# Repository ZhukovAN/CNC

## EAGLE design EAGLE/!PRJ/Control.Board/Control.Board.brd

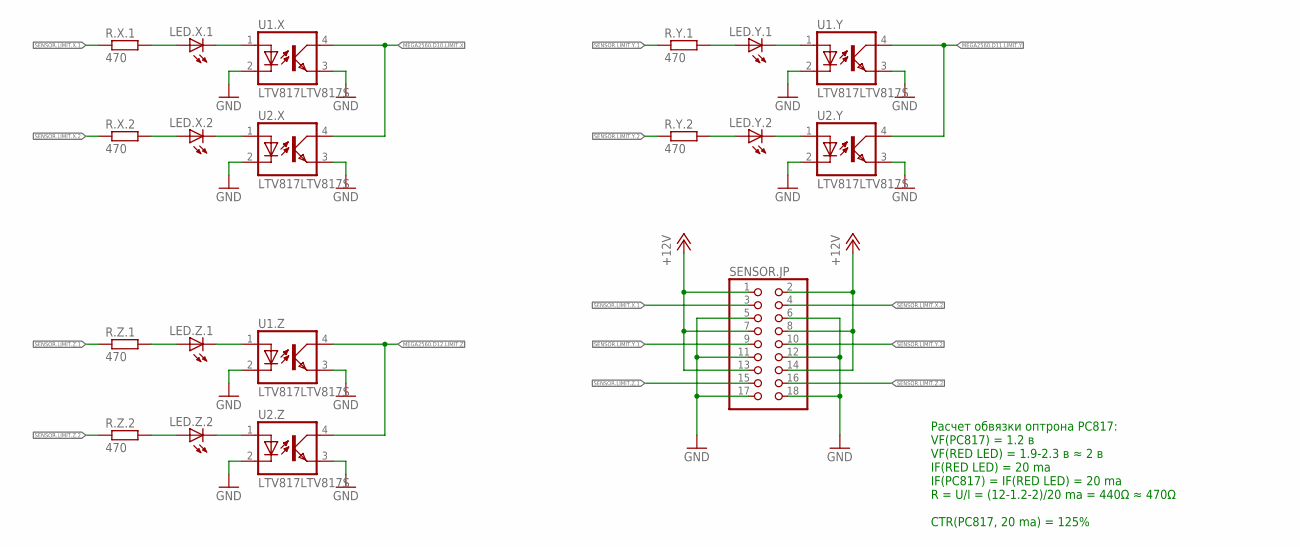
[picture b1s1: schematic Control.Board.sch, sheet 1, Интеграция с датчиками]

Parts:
LED.X.1, LED.X.2, LED.Y.1, LED.Y.2, LED.Z.1, LED.Z.2: LEDCHIPLED_1206; CHIPLED_1206
R.X.1, R.X.2, R.Y.1, R.Y.2, R.Z.1, R.Z.2: 470; M1206
SENSOR.JP: PINHD-2X9; 2X09
U1.X, U1.Y, U1.Z, U2.X, U2.Y, U2.Z: LTV817LTV817S; DIL4-SMD

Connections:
MEGA2560.D10.LIMIT.X: U1.X.4 (COL), U2.X.4 (COL); also elsewhere on the board
MEGA2560.D11.LIMIT.Y: U1.Y.4 (COL), U2.Y.4 (COL); also elsewhere on the board
MEGA2560.D12.LIMIT.Z: U1.Z.4 (COL), U2.Z.4 (COL); also elsewhere on the board
MEGA2560.GND: SENSOR.JP.5, SENSOR.JP.6, SENSOR.JP.11, SENSOR.JP.12, SENSOR.JP.17, SENSOR.JP.18, U1.X.2 (C), U1.X.3 (EMIT), U1.Y.2 (C), U1.Y.3 (EMIT), U1.Z.2 (C), U1.Z.3 (EMIT), U2.X.2 (C), U2.X.3 (EMIT), U2.Y.2 (C), U2.Y.3 (EMIT), U2.Z.2 (C), U2.Z.3 (EMIT); also elsewhere on the board
MEGA2560.VIN.12V: SENSOR.JP.1, SENSOR.JP.2, SENSOR.JP.7, SENSOR.JP.8, SENSOR.JP.13, SENSOR.JP.14; also elsewhere on the board
unnamed: LED.X.2.C, U2.X.1 (A)
unnamed: LED.Y.1.A, R.Y.1.2
unnamed: LED.X.1.A, R.X.1.2
unnamed: LED.X.2.A, R.X.2.2
unnamed: LED.X.1.C, U1.X.1 (A)
unnamed: LED.Y.2.A, R.Y.2.2
unnamed: LED.Y.2.C, U2.Y.1 (A)
unnamed: LED.Y.1.C, U1.Y.1 (A)
unnamed: LED.Z.1.A, R.Z.1.2
unnamed: LED.Z.2.A, R.Z.2.2
unnamed: LED.Z.2.C, U2.Z.1 (A)
unnamed: LED.Z.1.C, U1.Z.1 (A)
SENSOR.LIMIT.X.1: R.X.1.1, SENSOR.JP.3
SENSOR.LIMIT.X.2: R.X.2.1, SENSOR.JP.4
SENSOR.LIMIT.Y.1: R.Y.1.1, SENSOR.JP.9
SENSOR.LIMIT.Y.2: R.Y.2.1, SENSOR.JP.10
SENSOR.LIMIT.Z.1: R.Z.1.1, SENSOR.JP.15
SENSOR.LIMIT.Z.2: R.Z.2.1, SENSOR.JP.16

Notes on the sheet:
Расчет обвязки оптрона PC817: VF(PC817) = 1.2 в VF(RED LED) = 1.9-2.3 в ≈ 2 в IF(RED LED) = 20 ma IF(PC817) = IF(RED LED) = 20 ma R = U/I = (12-1.2-2)/20 ma = 440Ω ≈ 470Ω CTR(PC817, 20 ma) = 125%

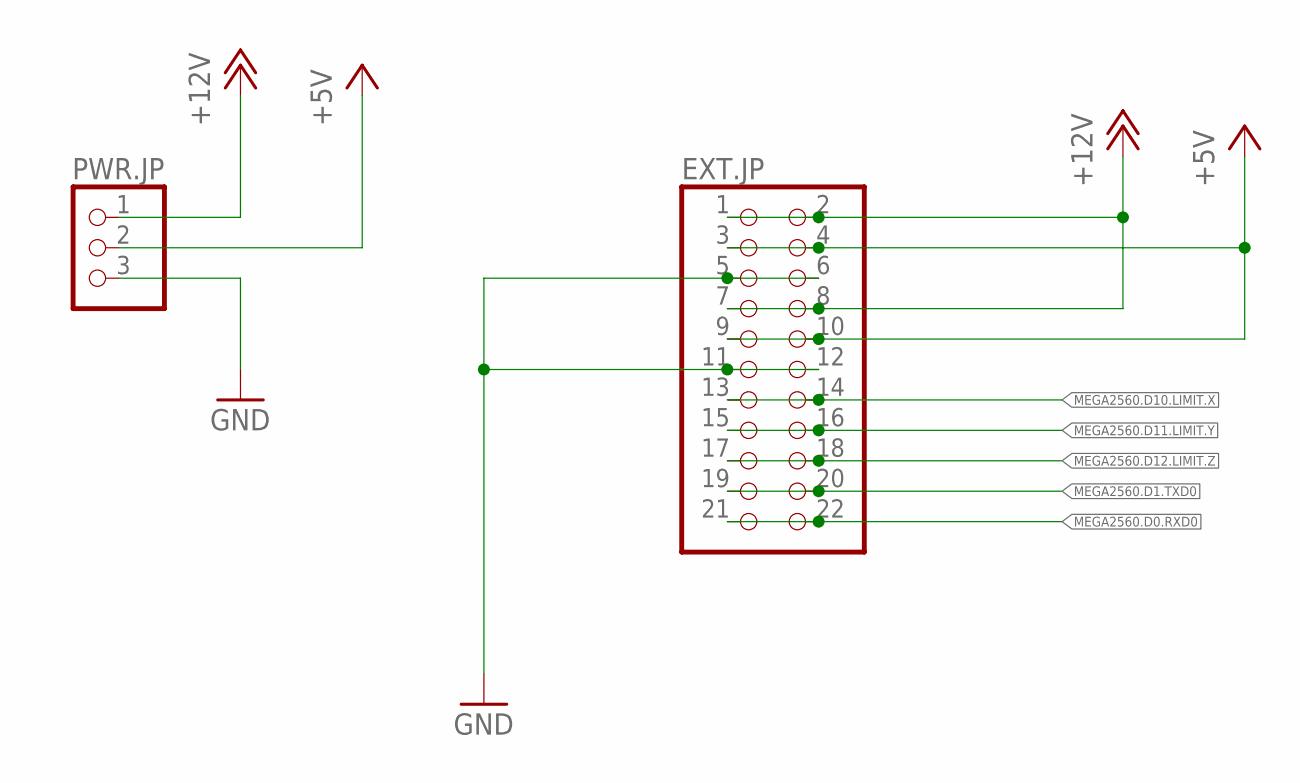
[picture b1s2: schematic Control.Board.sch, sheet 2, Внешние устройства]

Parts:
EXT.JP: PINHD-2X11; 2X11
PWR.JP: PINHD-1X3/90; 1X03/90

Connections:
+5V: EXT.JP.3, EXT.JP.4, EXT.JP.9, EXT.JP.10, PWR.JP.2; also elsewhere on the board
MEGA2560.D0.RXD0: EXT.JP.21, EXT.JP.22; also elsewhere on the board
MEGA2560.D1.TXD0: EXT.JP.19, EXT.JP.20; also elsewhere on the board
MEGA2560.D10.LIMIT.X: EXT.JP.13, EXT.JP.14; also elsewhere on the board
MEGA2560.D11.LIMIT.Y: EXT.JP.15, EXT.JP.16; also elsewhere on the board
MEGA2560.D12.LIMIT.Z: EXT.JP.17, EXT.JP.18; also elsewhere on the board
MEGA2560.GND: EXT.JP.5, EXT.JP.6, EXT.JP.11, EXT.JP.12, PWR.JP.3; also elsewhere on the board
MEGA2560.VIN.12V: EXT.JP.1, EXT.JP.2, EXT.JP.7, EXT.JP.8, PWR.JP.1; also elsewhere on the board

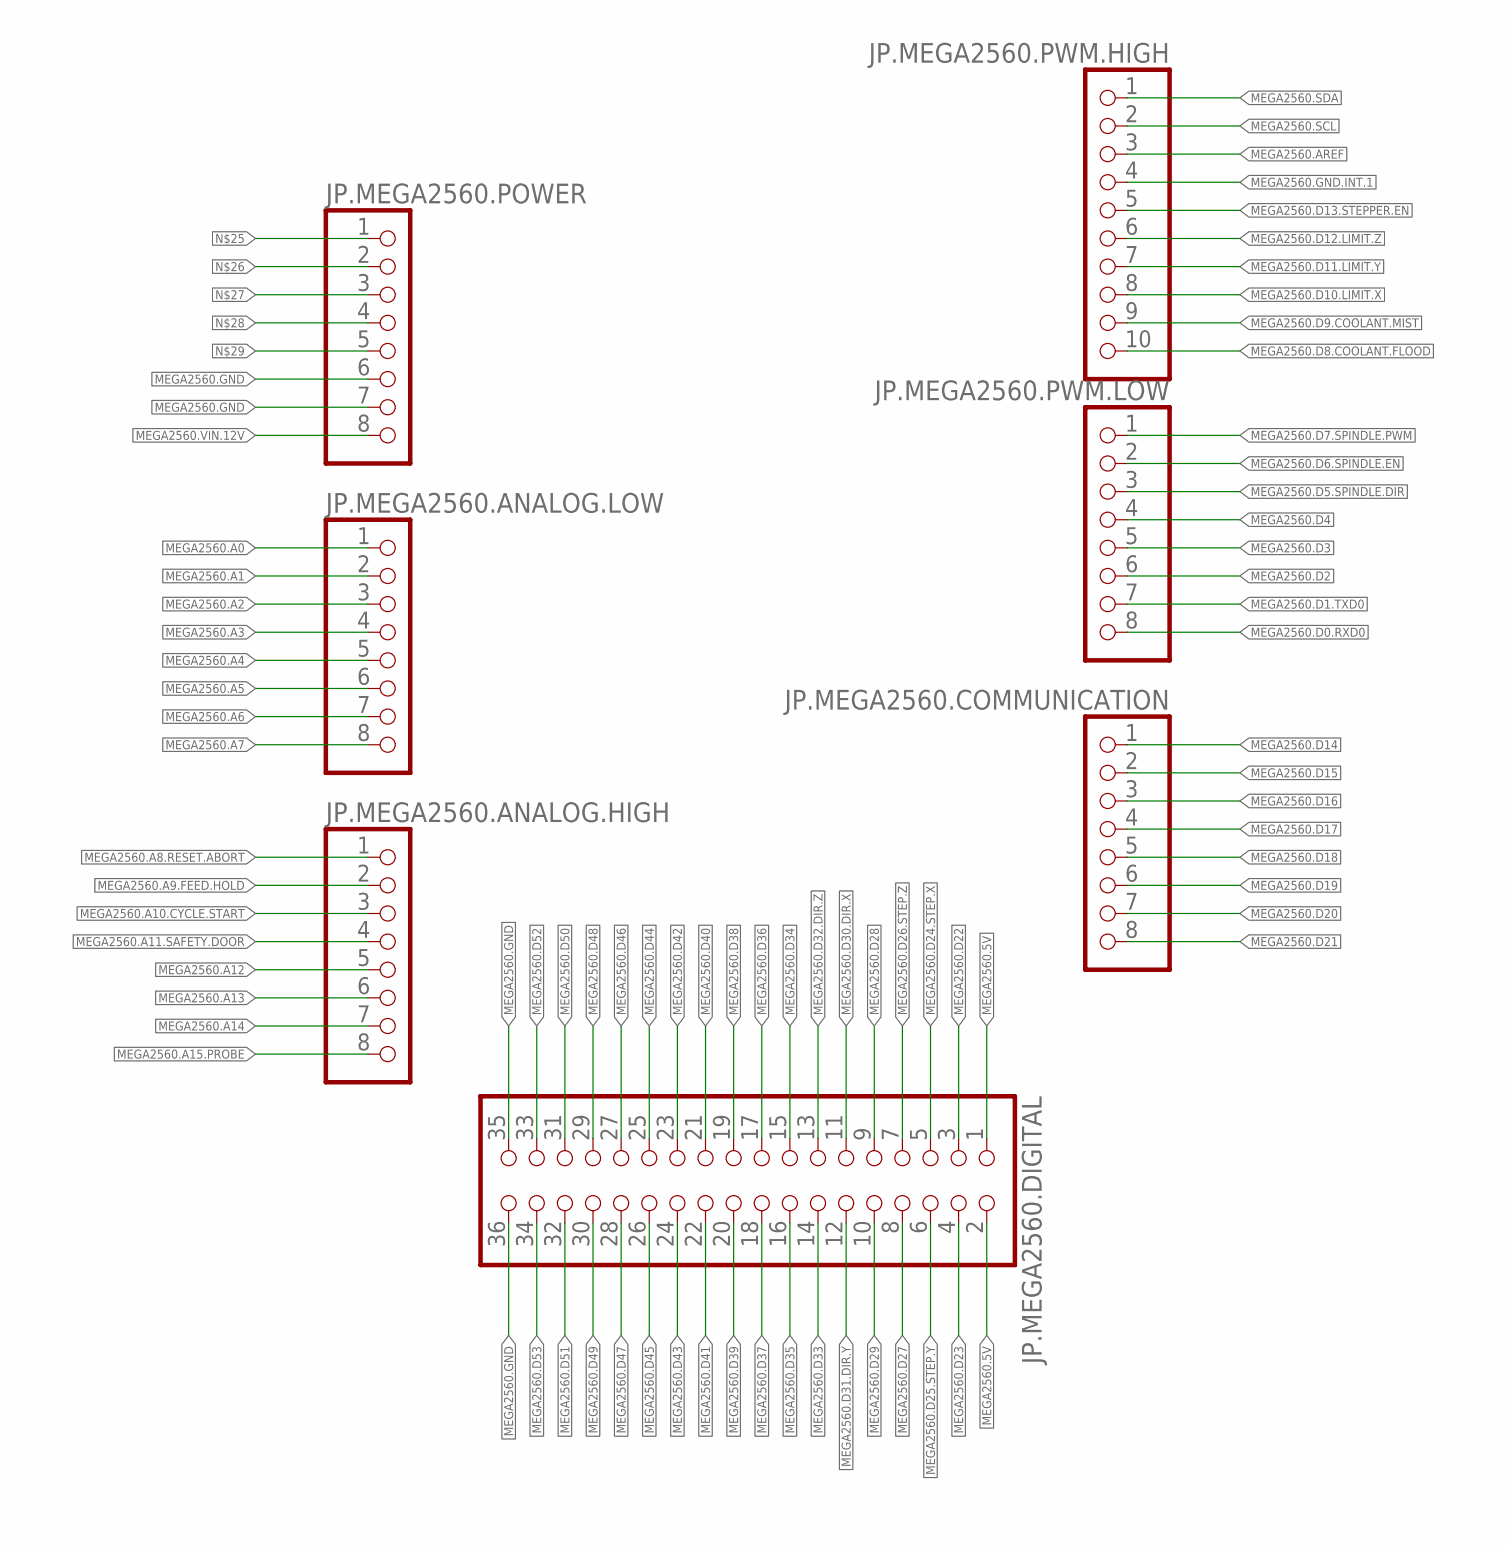
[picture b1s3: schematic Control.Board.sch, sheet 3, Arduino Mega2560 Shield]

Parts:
JP.MEGA2560.ANALOG.HIGH, JP.MEGA2560.ANALOG.LOW, JP.MEGA2560.COMMUNICATION, JP.MEGA2560.POWER, JP.MEGA2560.PWM.LOW: PINHD-1X8; 1X08
JP.MEGA2560.DIGITAL: PINHD-2X18; 2X18
JP.MEGA2560.PWM.HIGH: PINHD-1X10; 1X10

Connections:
MEGA2560.5V: JP.MEGA2560.DIGITAL.1, JP.MEGA2560.DIGITAL.2
MEGA2560.A0: JP.MEGA2560.ANALOG.LOW.1
MEGA2560.A1: JP.MEGA2560.ANALOG.LOW.2
MEGA2560.A2: JP.MEGA2560.ANALOG.LOW.3
MEGA2560.A3: JP.MEGA2560.ANALOG.LOW.4
MEGA2560.A4: JP.MEGA2560.ANALOG.LOW.5
MEGA2560.A5: JP.MEGA2560.ANALOG.LOW.6
MEGA2560.A6: JP.MEGA2560.ANALOG.LOW.7
MEGA2560.A7: JP.MEGA2560.ANALOG.LOW.8
MEGA2560.A8.RESET.ABORT: JP.MEGA2560.ANALOG.HIGH.1; also elsewhere on the board
MEGA2560.A9.FEED.HOLD: JP.MEGA2560.ANALOG.HIGH.2; also elsewhere on the board
MEGA2560.A10.CYCLE.START: JP.MEGA2560.ANALOG.HIGH.3; also elsewhere on the board
MEGA2560.A11.SAFETY.DOOR: JP.MEGA2560.ANALOG.HIGH.4; also elsewhere on the board
MEGA2560.A12: JP.MEGA2560.ANALOG.HIGH.5
MEGA2560.A13: JP.MEGA2560.ANALOG.HIGH.6
MEGA2560.A14: JP.MEGA2560.ANALOG.HIGH.7
MEGA2560.A15.PROBE: JP.MEGA2560.ANALOG.HIGH.8; also elsewhere on the board
MEGA2560.AREF: JP.MEGA2560.PWM.HIGH.3
MEGA2560.D0.RXD0: JP.MEGA2560.PWM.LOW.8; also elsewhere on the board
MEGA2560.D1.TXD0: JP.MEGA2560.PWM.LOW.7; also elsewhere on the board
MEGA2560.D2: JP.MEGA2560.PWM.LOW.6
MEGA2560.D3: JP.MEGA2560.PWM.LOW.5
MEGA2560.D4: JP.MEGA2560.PWM.LOW.4
MEGA2560.D5.SPINDLE.DIR: JP.MEGA2560.PWM.LOW.3; also elsewhere on the board
MEGA2560.D6.SPINDLE.EN: JP.MEGA2560.PWM.LOW.2; also elsewhere on the board
MEGA2560.D7.SPINDLE.PWM: JP.MEGA2560.PWM.LOW.1; also elsewhere on the board
MEGA2560.D8.COOLANT.FLOOD: JP.MEGA2560.PWM.HIGH.10; also elsewhere on the board
MEGA2560.D9.COOLANT.MIST: JP.MEGA2560.PWM.HIGH.9; also elsewhere on the board
MEGA2560.D10.LIMIT.X: JP.MEGA2560.PWM.HIGH.8; also elsewhere on the board
MEGA2560.D11.LIMIT.Y: JP.MEGA2560.PWM.HIGH.7; also elsewhere on the board
MEGA2560.D12.LIMIT.Z: JP.MEGA2560.PWM.HIGH.6; also elsewhere on the board
MEGA2560.D13.STEPPER.EN: JP.MEGA2560.PWM.HIGH.5; also elsewhere on the board
MEGA2560.D14: JP.MEGA2560.COMMUNICATION.1
MEGA2560.D15: JP.MEGA2560.COMMUNICATION.2
MEGA2560.D16: JP.MEGA2560.COMMUNICATION.3
MEGA2560.D17: JP.MEGA2560.COMMUNICATION.4
MEGA2560.D18: JP.MEGA2560.COMMUNICATION.5
MEGA2560.D19: JP.MEGA2560.COMMUNICATION.6
MEGA2560.D20: JP.MEGA2560.COMMUNICATION.7
MEGA2560.D21: JP.MEGA2560.COMMUNICATION.8
MEGA2560.D22: JP.MEGA2560.DIGITAL.3
MEGA2560.D23: JP.MEGA2560.DIGITAL.4
MEGA2560.D24.STEP.X: JP.MEGA2560.DIGITAL.5; also elsewhere on the board
MEGA2560.D25.STEP.Y: JP.MEGA2560.DIGITAL.6; also elsewhere on the board
MEGA2560.D26.STEP.Z: JP.MEGA2560.DIGITAL.7; also elsewhere on the board
MEGA2560.D27: JP.MEGA2560.DIGITAL.8
MEGA2560.D28: JP.MEGA2560.DIGITAL.9
MEGA2560.D29: JP.MEGA2560.DIGITAL.10
MEGA2560.D30.DIR.X: JP.MEGA2560.DIGITAL.11; also elsewhere on the board
MEGA2560.D31.DIR.Y: JP.MEGA2560.DIGITAL.12; also elsewhere on the board
MEGA2560.D32.DIR.Z: JP.MEGA2560.DIGITAL.13; also elsewhere on the board
MEGA2560.D33: JP.MEGA2560.DIGITAL.14
MEGA2560.D34: JP.MEGA2560.DIGITAL.15
MEGA2560.D35: JP.MEGA2560.DIGITAL.16
MEGA2560.D36: JP.MEGA2560.DIGITAL.17
MEGA2560.D37: JP.MEGA2560.DIGITAL.18
MEGA2560.D38: JP.MEGA2560.DIGITAL.19
MEGA2560.D39: JP.MEGA2560.DIGITAL.20
MEGA2560.D40: JP.MEGA2560.DIGITAL.21
MEGA2560.D41: JP.MEGA2560.DIGITAL.22
MEGA2560.D42: JP.MEGA2560.DIGITAL.23
MEGA2560.D43: JP.MEGA2560.DIGITAL.24
MEGA2560.D44: JP.MEGA2560.DIGITAL.25
MEGA2560.D45: JP.MEGA2560.DIGITAL.26
MEGA2560.D46: JP.MEGA2560.DIGITAL.27
MEGA2560.D47: JP.MEGA2560.DIGITAL.28
MEGA2560.D48: JP.MEGA2560.DIGITAL.29
MEGA2560.D49: JP.MEGA2560.DIGITAL.30
MEGA2560.D50: JP.MEGA2560.DIGITAL.31
MEGA2560.D51: JP.MEGA2560.DIGITAL.32
MEGA2560.D52: JP.MEGA2560.DIGITAL.33
MEGA2560.D53: JP.MEGA2560.DIGITAL.34
MEGA2560.GND: JP.MEGA2560.DIGITAL.35, JP.MEGA2560.DIGITAL.36, JP.MEGA2560.POWER.6, JP.MEGA2560.POWER.7; also elsewhere on the board
MEGA2560.GND.INT.1: JP.MEGA2560.PWM.HIGH.4
MEGA2560.SCL: JP.MEGA2560.PWM.HIGH.2
MEGA2560.SDA: JP.MEGA2560.PWM.HIGH.1
MEGA2560.VIN.12V: JP.MEGA2560.POWER.8; also elsewhere on the board

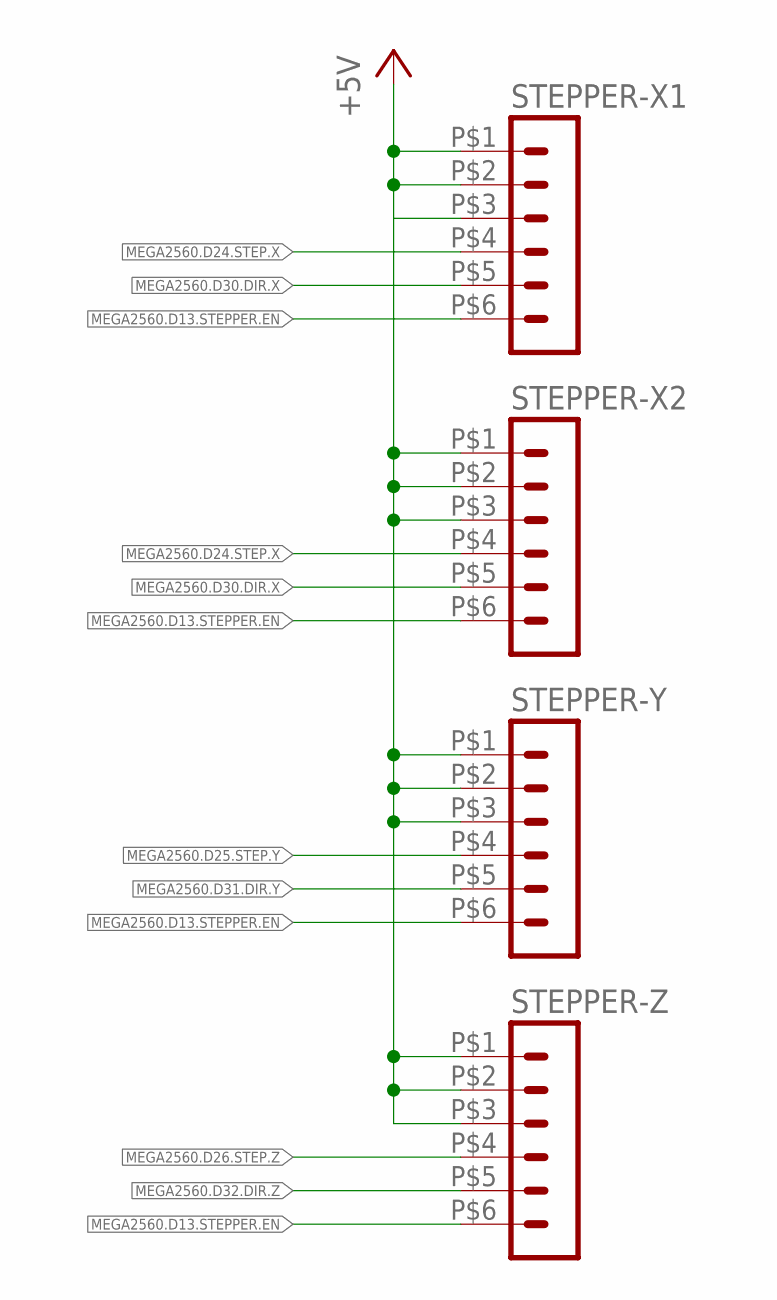
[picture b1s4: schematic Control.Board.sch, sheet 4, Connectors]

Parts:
STEPPER-X1, STEPPER-X2: HEADER_POS6_43045-0600; 43045-0600
STEPPER-Y: HEADER_POS6_43045-0600; 43045-0600
STEPPER-Z: HEADER_POS6_43045-0600; 43045-0600

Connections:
+5V: STEPPER-X1.P$1 (1), STEPPER-X1.P$2 (2), STEPPER-X1.P$3 (3), STEPPER-X2.P$1 (1), STEPPER-X2.P$2 (2), STEPPER-X2.P$3 (3), STEPPER-Y.P$1 (1), STEPPER-Y.P$2 (2), STEPPER-Y.P$3 (3), STEPPER-Z.P$1 (1), STEPPER-Z.P$2 (2), STEPPER-Z.P$3 (3); also elsewhere on the board
MEGA2560.D13.STEPPER.EN: STEPPER-X1.P$6 (6), STEPPER-X2.P$6 (6), STEPPER-Y.P$6 (6), STEPPER-Z.P$6 (6); also elsewhere on the board
MEGA2560.D24.STEP.X: STEPPER-X1.P$4 (4), STEPPER-X2.P$4 (4); also elsewhere on the board
MEGA2560.D25.STEP.Y: STEPPER-Y.P$4 (4); also elsewhere on the board
MEGA2560.D26.STEP.Z: STEPPER-Z.P$4 (4); also elsewhere on the board
MEGA2560.D30.DIR.X: STEPPER-X1.P$5 (5), STEPPER-X2.P$5 (5); also elsewhere on the board
MEGA2560.D31.DIR.Y: STEPPER-Y.P$5 (5); also elsewhere on the board
MEGA2560.D32.DIR.Z: STEPPER-Z.P$5 (5); also elsewhere on the board

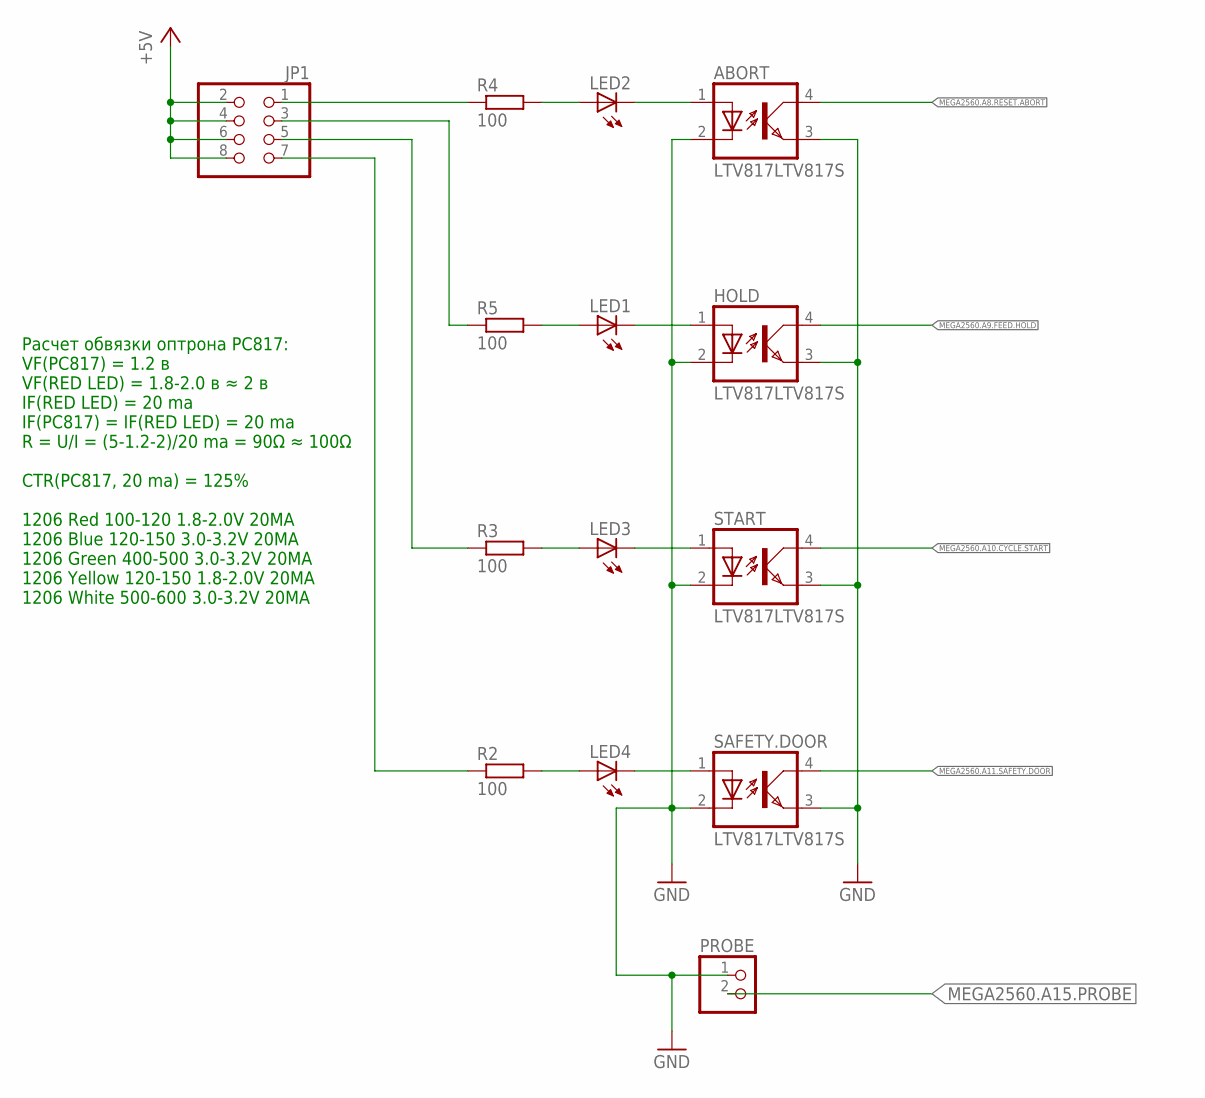
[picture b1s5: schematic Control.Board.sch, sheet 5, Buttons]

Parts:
ABORT: LTV817LTV817S; DIL4-SMD
HOLD: LTV817LTV817S; DIL4-SMD
JP1: PINHD-2X4; 2X04
LED1, LED2, LED3, LED4: LEDCHIPLED_1206; CHIPLED_1206
PROBE: PINHD-1X2; 1X02
R2, R3, R4, R5: 100; M1206
SAFETY.DOOR: LTV817LTV817S; DIL4-SMD
START: LTV817LTV817S; DIL4-SMD

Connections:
+5V: JP1.2, JP1.4, JP1.6, JP1.8; also elsewhere on the board
GND: ABORT.2 (C), HOLD.2 (C), PROBE.1, SAFETY.DOOR.2 (C), START.2 (C)
MEGA2560.A8.RESET.ABORT: ABORT.4 (COL); also elsewhere on the board
MEGA2560.A9.FEED.HOLD: HOLD.4 (COL); also elsewhere on the board
MEGA2560.A10.CYCLE.START: START.4 (COL); also elsewhere on the board
MEGA2560.A11.SAFETY.DOOR: SAFETY.DOOR.4 (COL); also elsewhere on the board
MEGA2560.A15.PROBE: PROBE.2; also elsewhere on the board
MEGA2560.GND: ABORT.3 (EMIT), HOLD.3 (EMIT), SAFETY.DOOR.3 (EMIT), START.3 (EMIT); also elsewhere on the board
unnamed: ABORT.1 (A), LED2.C
unnamed: JP1.3, R5.1
unnamed: JP1.5, R3.1
unnamed: HOLD.1 (A), LED1.C
unnamed: LED1.A, R5.2
unnamed: LED2.A, R4.2
unnamed: JP1.1, R4.1
unnamed: JP1.7, R2.1
unnamed: LED3.A, R3.2
unnamed: LED3.C, START.1 (A)
unnamed: LED4.C, SAFETY.DOOR.1 (A)
unnamed: LED4.A, R2.2

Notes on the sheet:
Расчет обвязки оптрона PC817: VF(PC817) = 1.2 в VF(RED LED) = 1.8-2.0 в ≈ 2 в IF(RED LED) = 20 ma IF(PC817) = IF(RED LED) = 20 ma R = U/I = (5-1.2-2)/20 ma = 90Ω ≈ 100Ω CTR(PC817, 20 ma) = 125% 1206 Red 100-120 1.8-2.0V 20MA 1206 Blue 120-150 3.0-3.2V 20MA 1206 Green 400-500 3.0-3.2V 20MA 1206 Yell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

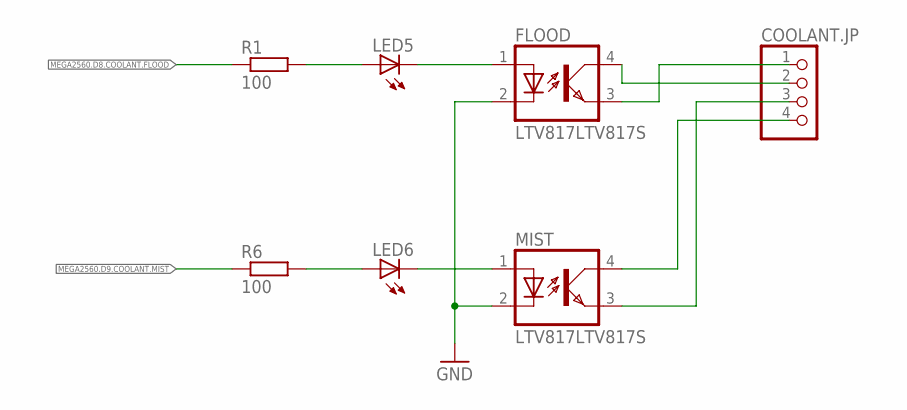
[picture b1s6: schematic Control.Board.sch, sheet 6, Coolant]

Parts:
COOLANT.JP: PINHD-1X4/90; 1X04/90
FLOOD: LTV817LTV817S; DIL4-SMD
LED5, LED6: LEDCHIPLED_1206; CHIPLED_1206
MIST: LTV817LTV817S; DIL4-SMD
R1, R6: 100; M1206

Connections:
MEGA2560.D8.COOLANT.FLOOD: R1.1; also elsewhere on the board
MEGA2560.D9.COOLANT.MIST: R6.1; also elsewhere on the board
MEGA2560.GND: FLOOD.2 (C), MIST.2 (C); also elsewhere on the board
unnamed: LED5.A, R1.2
unnamed: FLOOD.1 (A), LED5.C
unnamed: COOLANT.JP.1, FLOOD.3 (EMIT)
unnamed: COOLANT.JP.3, MIST.3 (EMIT)
unnamed: COOLANT.JP.2, FLOOD.4 (COL)
unnamed: COOLANT.JP.4, MIST.4 (COL)
unnamed: LED6.A, R6.2
unnamed: LED6.C, MIST.1 (A)

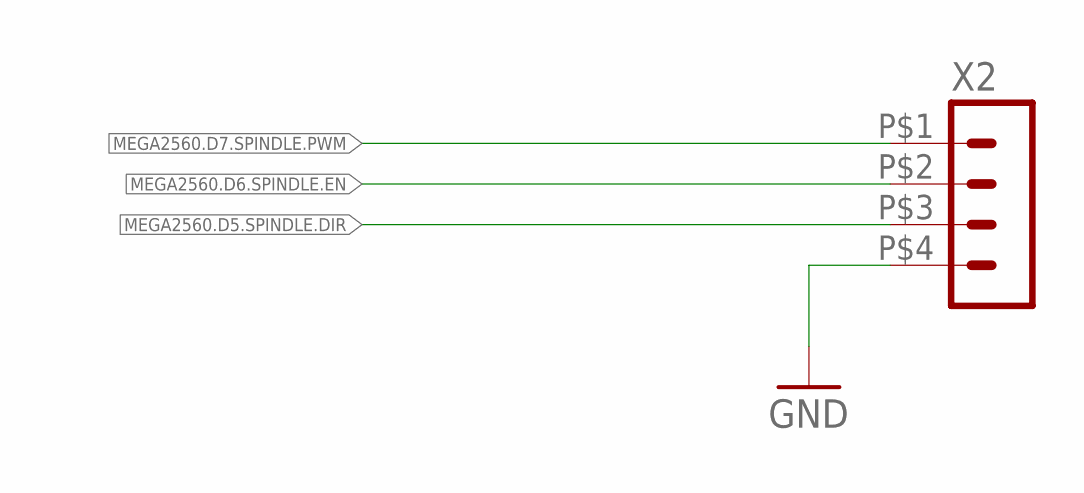
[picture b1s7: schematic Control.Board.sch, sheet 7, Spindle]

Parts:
X2: HEADER_POS4_43045-0401; 43045-0400

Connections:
MEGA2560.D5.SPINDLE.DIR: X2.P$3 (3); also elsewhere on the board
MEGA2560.D6.SPINDLE.EN: X2.P$2 (2); also elsewhere on the board
MEGA2560.D7.SPINDLE.PWM: X2.P$1 (1); also elsewhere on the board
MEGA2560.GND: X2.P$4 (4); also elsewhere on the board

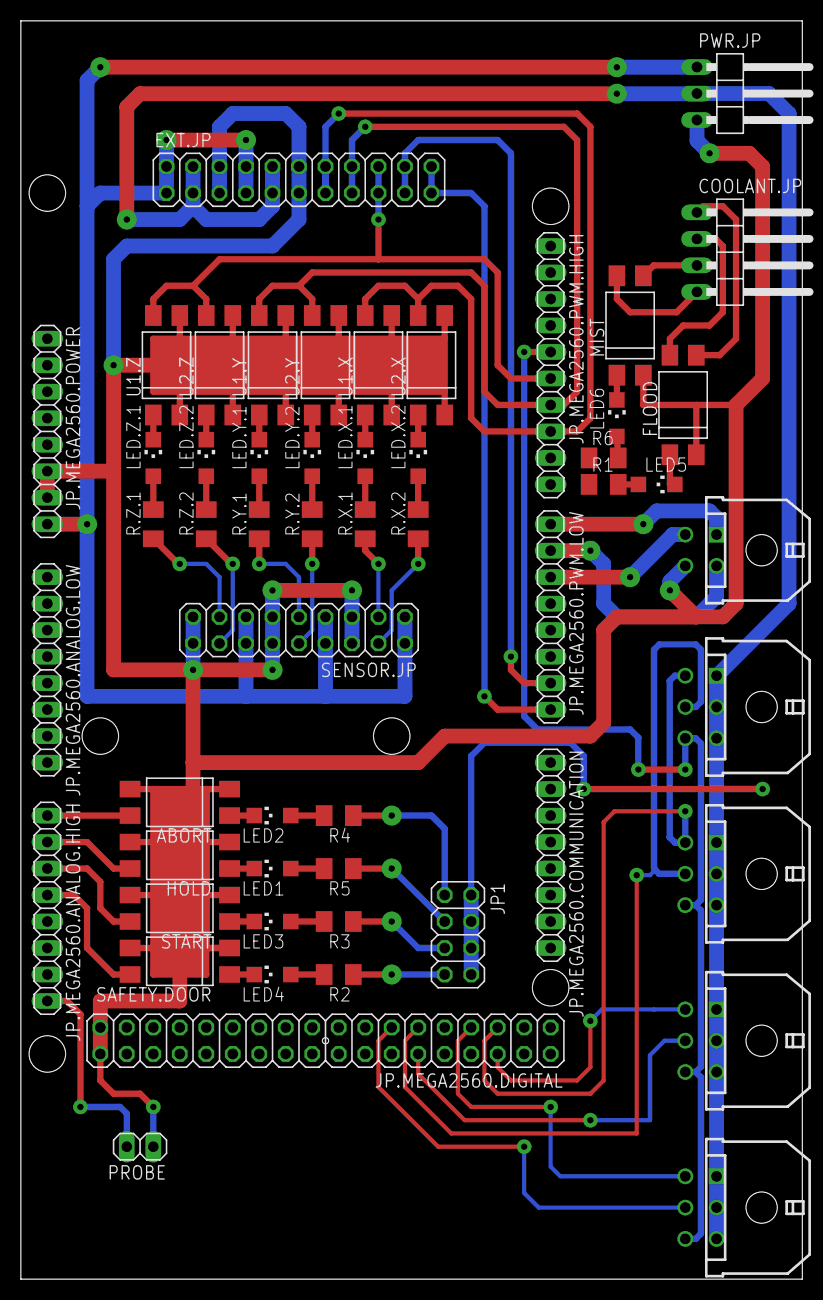
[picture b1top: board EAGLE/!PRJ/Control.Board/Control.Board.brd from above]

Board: 2 copper layers, 74.9 x 120.7 mm, 54 parts (0 on the bottom side), 65 nets.

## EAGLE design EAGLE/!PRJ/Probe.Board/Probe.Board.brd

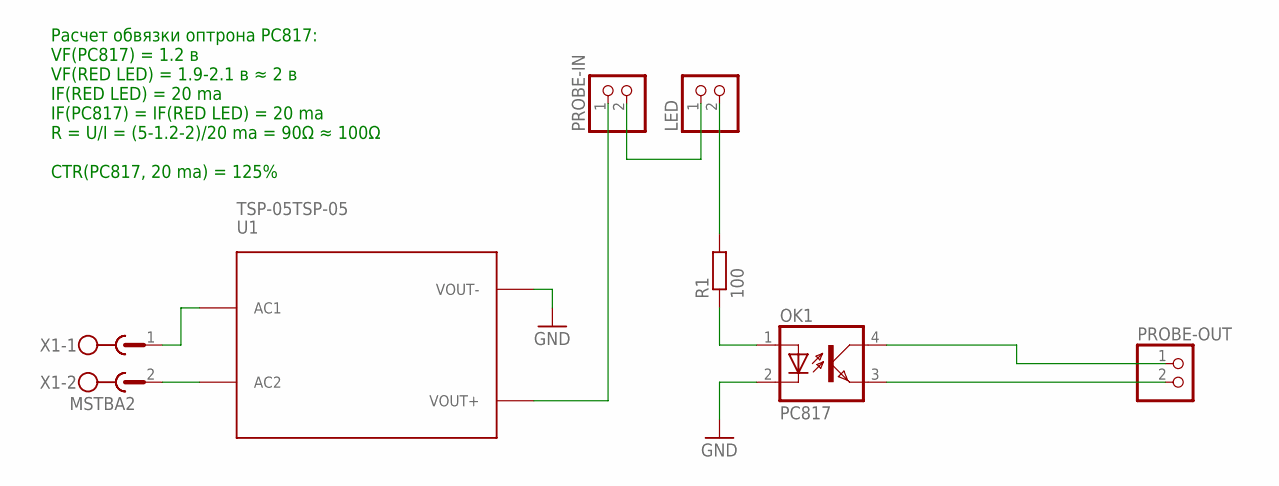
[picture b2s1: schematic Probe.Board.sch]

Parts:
LED: PINHD-1X2/90; 1X02/90
OK1: PC817; DIL04
PROBE-IN: PINHD-1X2/90; 1X02/90
PROBE-OUT: PINHD-1X2/90; 1X02/90
R1: 100; 0207/12
U1: TSP-05TSP-05; TSP-05
X1: MSTBA2

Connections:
GND: OK1.2 (C), U1.P$3 (VOUT-)
unnamed: U1.P$2 (AC2), X1.2
unnamed: U1.P$1 (AC1), X1.1
unnamed: OK1.3 (EMIT), PROBE-OUT.2
unnamed: OK1.4 (COL), PROBE-OUT.1
unnamed: OK1.1 (A), R1.1
unnamed: LED.2, R1.2
unnamed: LED.1, PROBE-IN.2
unnamed: PROBE-IN.1, U1.P$4 (VOUT+)

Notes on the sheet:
Расчет обвязки оптрона PC817: VF(PC817) = 1.2 в VF(RED LED) = 1.9-2.1 в ≈ 2 в IF(RED LED) = 20 ma IF(PC817) = IF(RED LED) = 20 ma R = U/I = (5-1.2-2)/20 ma = 90Ω ≈ 100Ω CTR(PC817, 20 ma) = 125%

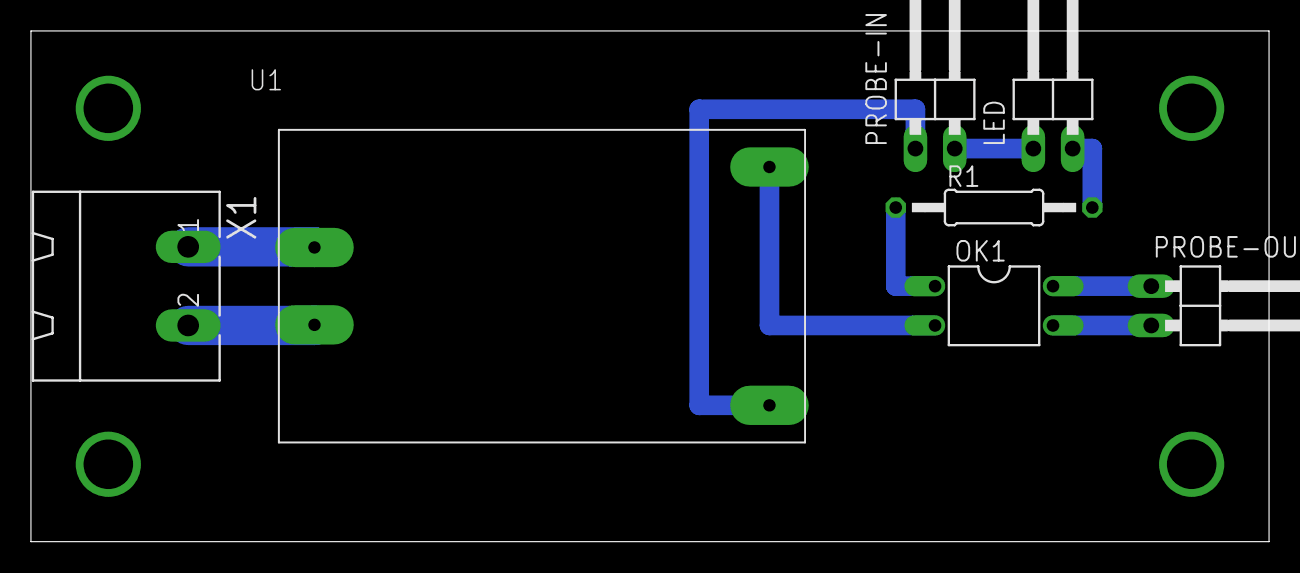
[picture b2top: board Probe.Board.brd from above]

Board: 2 copper layers, 80.0 x 33.0 mm, 7 parts (0 on the bottom side), 9 nets.

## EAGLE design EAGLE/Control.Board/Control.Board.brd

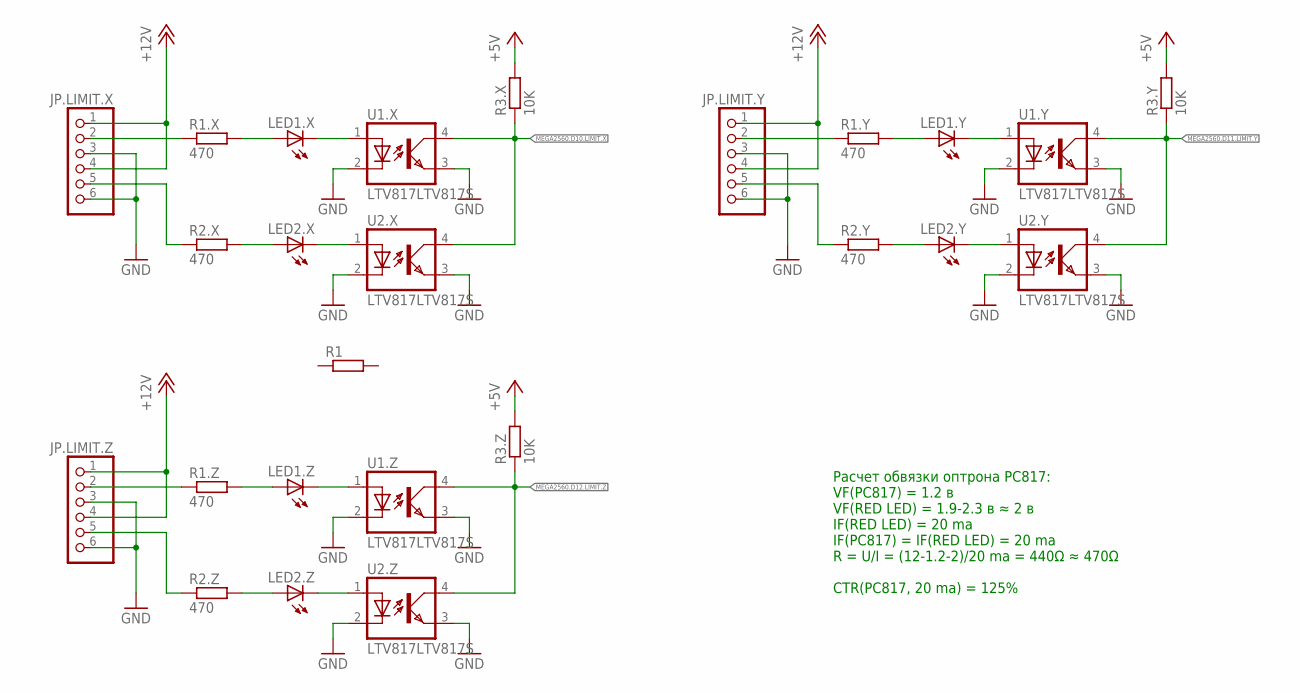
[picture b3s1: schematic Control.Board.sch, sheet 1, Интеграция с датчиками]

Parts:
JP.LIMIT.X, JP.LIMIT.Y, JP.LIMIT.Z: PINHD-1X6; 1X06
LED1.X, LED1.Y, LED1.Z, LED2.X, LED2.Y, LED2.Z: LEDCHIPLED_0805; CHIPLED_0805
R1: R-EU_M1206; M1206
R1.X, R1.Y, R1.Z, R2.X, R2.Y, R2.Z: 470; M0805
R3.X, R3.Y, R3.Z: 10K; M0805
U1.X, U1.Y, U1.Z, U2.X, U2.Y, U2.Z: LTV817LTV817S; DIL4-SMD

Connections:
+5V: R3.X.2, R3.Y.2, R3.Z.2; also elsewhere on the board
+12V: JP.LIMIT.X.1, JP.LIMIT.X.4, JP.LIMIT.Y.1, JP.LIMIT.Y.4, JP.LIMIT.Z.1, JP.LIMIT.Z.4
GND: JP.LIMIT.X.3, JP.LIMIT.X.6, JP.LIMIT.Y.3, JP.LIMIT.Y.6, JP.LIMIT.Z.3, JP.LIMIT.Z.6, U1.X.2 (C), U1.X.3 (EMIT), U1.Y.2 (C), U1.Y.3 (EMIT), U1.Z.2 (C), U1.Z.3 (EMIT), U2.X.2 (C), U2.X.3 (EMIT), U2.Y.2 (C), U2.Y.3 (EMIT), U2.Z.2 (C), U2.Z.3 (EMIT); also elsewhere on the board
MEGA2560.D10.LIMIT.X: R3.X.1, U1.X.4 (COL), U2.X.4 (COL); also elsewhere on the board
MEGA2560.D11.LIMIT.Y: R3.Y.1, U1.Y.4 (COL), U2.Y.4 (COL); also elsewhere on the board
MEGA2560.D12.LIMIT.Z: R3.Z.1, U1.Z.4 (COL), U2.Z.4 (COL); also elsewhere on the board
unnamed: LED2.X.C, U2.X.1 (A)
unnamed: JP.LIMIT.Y.2, R1.Y.1
unnamed: LED1.Y.A, R1.Y.2
unnamed: JP.LIMIT.X.2, R1.X.1
unnamed: LED1.X.A, R1.X.2
unnamed: JP.LIMIT.X.5, R2.X.1
unnamed: LED2.X.A, R2.X.2
unnamed: LED1.X.C, U1.X.1 (A)
unnamed: JP.LIMIT.Y.5, R2.Y.1
unnamed: LED2.Y.A, R2.Y.2
unnamed: LED2.Y.C, U2.Y.1 (A)
unnamed: LED1.Y.C, U1.Y.1 (A)
unnamed: JP.LIMIT.Z.2, R1.Z.1
unnamed: LED1.Z.A, R1.Z.2
unnamed: JP.LIMIT.Z.5, R2.Z.1
unnamed: LED2.Z.A, R2.Z.2
unnamed: LED2.Z.C, U2.Z.1 (A)
unnamed: LED1.Z.C, U1.Z.1 (A)

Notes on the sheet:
Расчет обвязки оптрона PC817: VF(PC817) = 1.2 в VF(RED LED) = 1.9-2.3 в ≈ 2 в IF(RED LED) = 20 ma IF(PC817) = IF(RED LED) = 20 ma R = U/I = (12-1.2-2)/20 ma = 440Ω ≈ 470Ω CTR(PC817, 20 ma) = 125%

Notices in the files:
parts and their libraries:
SparkFun-Aesthetics: Licensing: Creative Commons ShareAlike 4.0 International - https://creativecommons.org/licenses/by-sa/4.0
